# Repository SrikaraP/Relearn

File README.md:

# Relearn

### The AI-Powered Education OS

Relearn is an AI-powered platform that brings students, teachers, and parents into one connected learning ecosystem.

Instead of juggling multiple apps for studying, assignments, communication, and progress tracking, Relearn combines everything into a single intelligent platform.

## Why Relearn?

Education is fragmented.

Students struggle to stay organized, teachers spend hours on repetitive tasks, and parents often lack visibility into academic progress.

Relearn uses AI to simplify learning, automate workflows, and provide personalized insights for everyone involved.

## Key Features

### For Institutions

* Exan Paper Scanning Tool
* Secure File Transfers
* Student File Tracking
* Student Progress Tracking

### For Students

* Personalized learning roadmaps
* AI study assistant
* Smart summaries, flashcards, and quizzes
* Progress tracking and goal setting

### For Teachers

* Question paper and answer sheet analysis
* Performance insights and learning-gap detection
* Automated feedback generation
* Classroom management tools

### For Parents

* Real-time academic visibility
* Progress monitoring
* Personalized learning recommendations

## ReLens

### ReLens Lite

A student-focused scanner that converts notes and worksheets into:

* Summaries
* Flashcards
* Quizzes
* Revision resources

### ReLens Edu

A teacher-focused scanner that analyzes:

* Question papers
* Answer sheets
* Student performance
* Common mistakes and learning gaps

## Tech Stack

* React
* TypeScript
* Vite
* Google Gemini
* OCR & Multimodal AI
* Custom PCB Scanner Hardware

## Vision

To build the operating system for education.

## An insider Look Into the Project

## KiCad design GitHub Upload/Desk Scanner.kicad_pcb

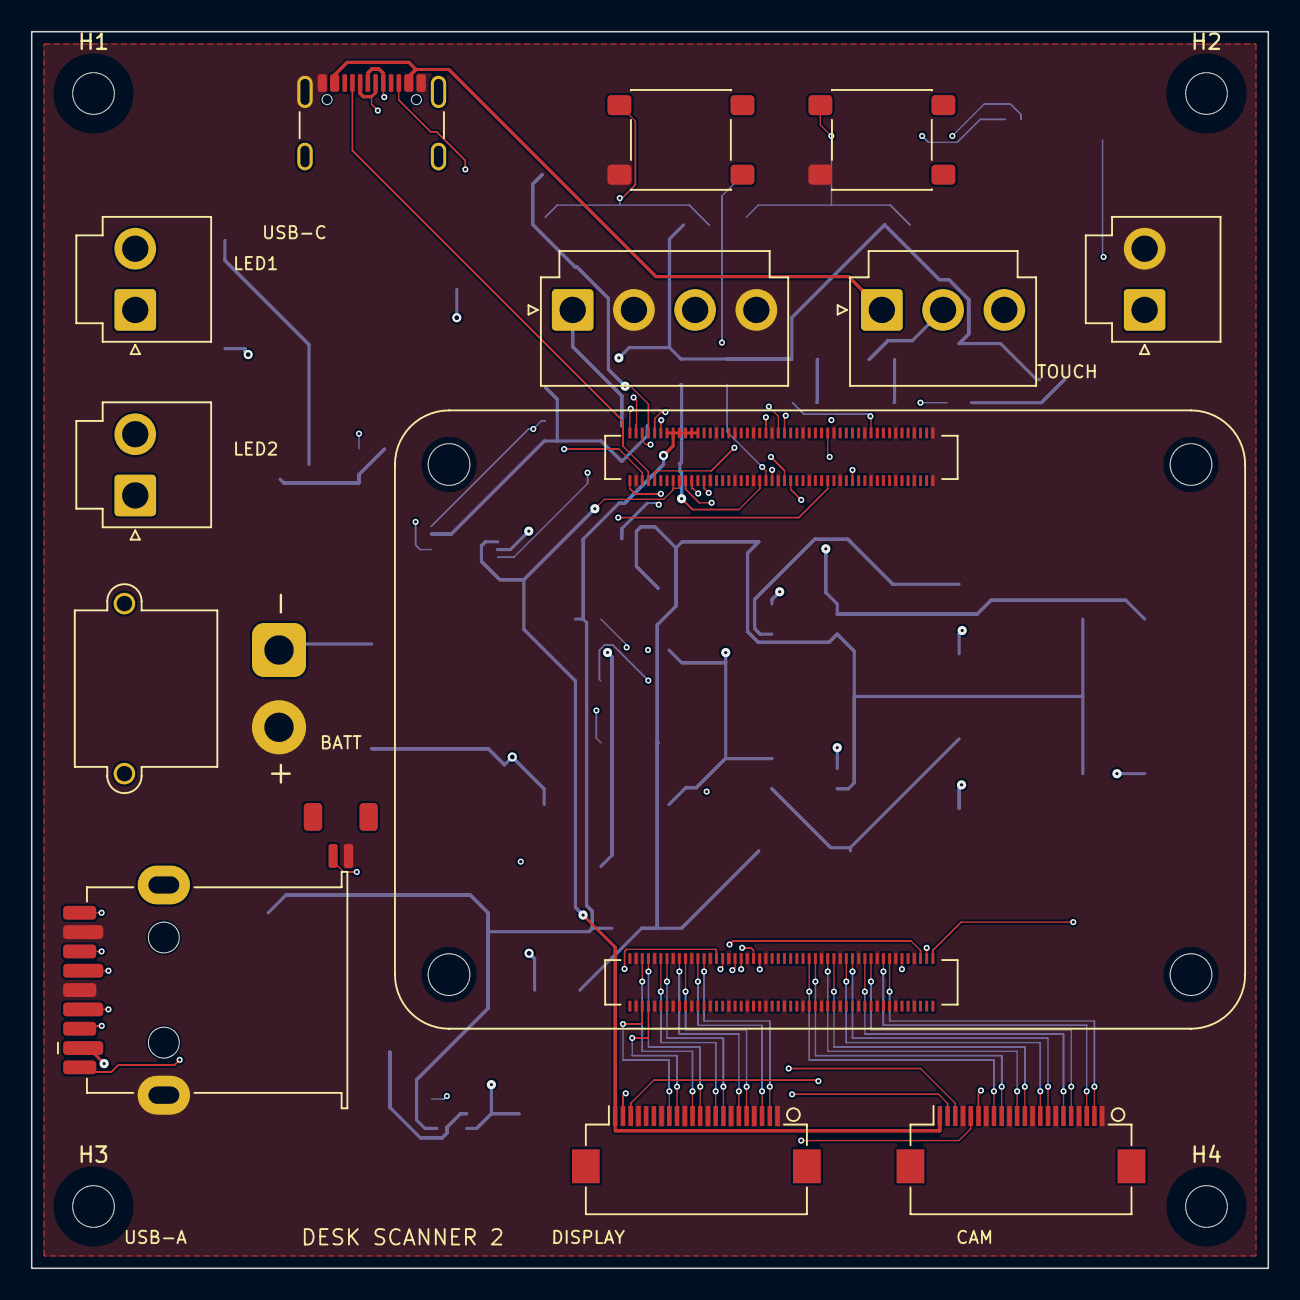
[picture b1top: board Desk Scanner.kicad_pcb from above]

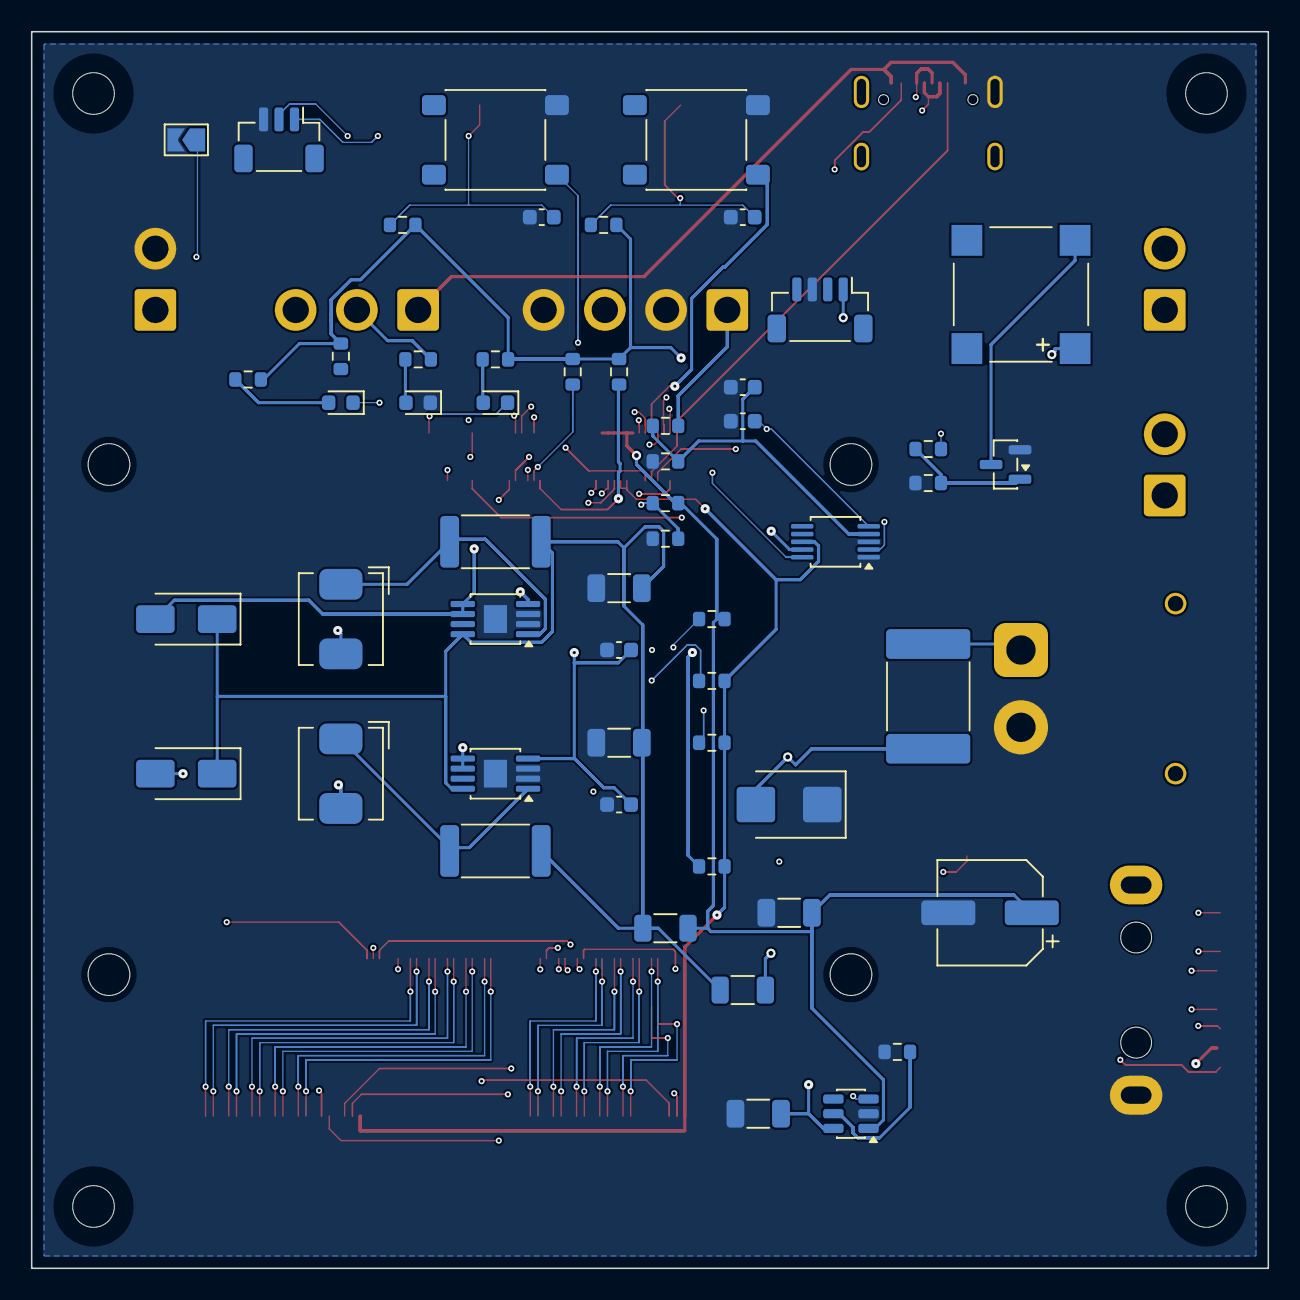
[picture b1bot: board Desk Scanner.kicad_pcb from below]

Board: 4 copper layers, 80.0 x 80.0 mm, 72 parts (54 on the bottom side), 78 nets.

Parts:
BT1: Wired RTC cell input; JST_SH_BM02B-SRSS-TB_1x02-1MP_P1.00mm_Vertical
BZ1: 5V active buzzer; PUIAudio_SMT_0825_S_4_R
C1: 10uF USB VBUS; C_1206_3216Metric
C2: 100uF bulk; CP_Elec_6.3x5.8
C3: 10uF; C_1206_3216Metric
C4, C5: 10uF 50V X7R; C_1206_3216Metric
C6, C7: 1nF soft-start; C_0603_1608Metric
C8, C9: 100nF debounce; C_0603_1608Metric
C10: 100nF BAT filter; C_0603_1608Metric
C11: 100nF 5V filter; C_0603_1608Metric
D2: SMBJ16A TVS; D_SMB
D3, D4: SS34 Schottky; D_SMA
D5: ACT LED green; LED_0603_1608Metric
D6: Power LED; LED_0603_1608Metric
D7: CM5 PWR status LED; LED_0603_1608Metric
F1: 7.5A battery fuse; Fuse_2920_7451Metric
H1, H2, H3, H4: M2.5; MountingHole_2.7mm_M2.5_DIN965
J1: USB-C USB2 Data + 5V Input; USB_C_Receptacle_GCT_USB4105-xx-A_16P_TopMnt_Horizontal
J2: USB-A Host USB3; USB3_A_Receptacle_Wuerth_692122030100
J3: Camera FFC - Raspberry Pi Camera Module 3 AF; Hirose_FH12-22S-0.5SH_1x22-1MP_P0.50mm_Horizontal
J4: Display FFC - Raspberry Pi Touch Display 2; Hirose_FH12-22S-0.5SH_1x22-1MP_P0.50mm_Horizontal
J5: Display 5V Power; JST_VH_B2P-VH_1x02_P3.96mm_Vertical
J6: 3S protected Li-ion pack input XT30; AMASS_XT30PW-M_1x02_P2.50mm_Horizontal
J7: 5V 6A buck regulator module; JST_VH_B4P-VH_1x04_P3.96mm_Vertical
J8: High-current 5V source selector; JST_VH_B3P-VH_1x03_P3.96mm_Vertical
J9: LED bar 1 output; JST_VH_B2P-VH_1x02_P3.96mm_Vertical
J10: LED bar 2 output; JST_VH_B2P-VH_1x02_P3.96mm_Vertical
J11: 5V PWM fan; JST_SH_BM04B-SRSS-TB_1x04-1MP_P1.00mm_Vertical
J12: UART debug 3-pin; JST_SH_BM03B-SRSS-TB_1x03-1MP_P1.00mm_Vertical
JP1: USB OTG ID strap - leave open for device mode; SolderJumper-2_P1.3mm_Open_TrianglePad1.0x1.5mm
L1, L2: 47uH >=2A shielded; L_Bourns_SRP5030CC
Q1: 2N7002 buzzer low-side; SOT-23
R1: 10k USB ILIM set; R_0603_1608Metric
R2: 10k PMIC enable pull-up; R_0603_1608Metric
R3: 10k WLAN enable pull-up; R_0603_1608Metric
R4: 10k Bluetooth enable pull-up; R_0603_1608Metric
R5: 10k boot pull-up; R_0603_1608Metric
R6: 0R LED_SUPPLY from +5V_SYS; R_1206_3216Metric
R7: 0R DNP LED_SUPPLY from BAT_FUSED; R_1206_3216Metric
R8, R9: 0.15R 1% 0.5W LED sense; R_2512_6332Metric
R10, R11: 10k; R_0603_1608Metric
R12: 100R gate; R_0603_1608Metric
R13: 100k gate pulldown; R_0603_1608Metric
R14: 1k ACT; R_0603_1608Metric
R15: 1k PWR; R_0603_1608Metric
R16: 10k tach pull-up; R_0603_1608Metric
R17: 2.2k SDA pull-up; R_0603_1608Metric
R18: 2.2k SCL pull-up; R_0603_1608Metric
R19: 100k BAT top; R_0603_1608Metric
R20: 22k BAT bottom; R_0603_1608Metric
R21: 47k 5V top; R_0603_1608Metric
R22: 47k 5V bottom; R_0603_1608Metric
R23: 1k CM5 PWR; R_0603_1608Metric
SW1: Scan/Capture button; SW_SPST_PTS645Sx43SMTR92
SW2: Lighting level button; SW_SPST_PTS645Sx43SMTR92
SW3: nRPIBOOT recovery; SW_SPST_PTS645Sx43SMTR92
SW4: CM5 power button; SW_SPST_PTS645Sx43SMTR92
U1: Raspberry Pi CM5 Wireless 8GB/64GB eMMC; Raspberry-Pi-5-Compute-Module
U2: AP2553W6 USB Host Power Switch; SOT-23-6
U3: AL8860MP LED driver 1; MSOP-8-1EP_3x3mm_P0.65mm_EP1.5x1.8mm
U4: AL8860MP LED driver 2; MSOP-8-1EP_3x3mm_P0.65mm_EP1.5x1.8mm
U5: ADS1115 battery/system monitor; TSSOP-10_3x3mm_P0.5mm

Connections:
/+3V3_CM5: J3.22, J4.22, R3.1, R4.1, R5.1, R10.1, R11.1, R14.1, R16.1, R17.1, R18.1, R23.1, U1.84, U1.86, U5.8
/+5V_BATREG: J7.3, J8.3
/+5V_SYS: BZ1.1, C2.1, C3.1, J5.1, J8.2, J11.1, R2.1, R6.1, R15.1, R21.1, U1.77, U1.79, U1.81, U1.83, U1.85, U1.87, U2.1
/+5V_USBC: J1.A4, J1.A9, J1.B4, J1.B9, J8.1
/ACT_LED_A: D5.2, R14.2
/ADC_ALERT: U1.54, U5.2
/BAT_FUSED: D2.2, F1.2, J7.1, R7.1, R19.1
/BAT_RAW: F1.1, J6.1
/BAT_SENSE: C10.1, R19.2, R20.1, U5.4
/BTN_LED_MODE: C9.1, R11.2, SW2.1, U1.48
/BTN_SCAN: C8.1, R10.2, SW1.1, U1.50
/BT_nDISABLE: R4.2, U1.91
/BUZZER_GATE: Q1.1, R12.2, R13.1
/BUZZER_GPIO: R12.1, U1.28
/BUZZER_LOW: BZ1.2, Q1.3
/CAM_GPIO0: J3.17, U1.97
/CAM_GPIO1: J3.18, U1.100
/CM5_PWR_LED_A: D7.2, R23.2
/DPHY0_C_N: J3.8, U1.127
/DPHY0_C_P: J3.9, U1.129
/DPHY0_D0_N: J3.2, U1.115
/DPHY0_D0_P: J3.3, U1.117
/DPHY0_D1_N: J3.5, U1.121
/DPHY0_D1_P: J3.6, U1.123
/DPHY0_D2_N: J3.11, U1.133
/DPHY0_D2_P: J3.12, U1.135
/DPHY0_D3_N: J3.14, U1.139
/DPHY0_D3_P: J3.15, U1.141
/DPHY1_C_N: J4.8, U1.187
/DPHY1_C_P: J4.9, U1.189
/DPHY1_D0_N: J4.2, U1.175
/DPHY1_D0_P: J4.3, U1.177
/DPHY1_D1_N: J4.5, U1.181
/DPHY1_D1_P: J4.6, U1.183
/DPHY1_D2_N: J4.11, U1.193
/DPHY1_D2_P: J4.12, U1.195
/DPHY1_D3_N: J4.14, U1.194
/DPHY1_D3_P: J4.15, U1.196
/GND: BT1.2, C1.2, C2.2, C3.2, C4.2, C5.2, C6.2, C7.2, C8.2, C9.2, C10.2, C11.2, D2.1, D6.1, J1.A1, J1.A12, J1.B1, J1.B12, J1.SH, J2.4, J2.7, J2.SH, J3.1, J3.4, J3.7, J3.10, J3.13, J3.16, J3.19, J4.1, J4.4, J4.7, J4.10, J4.13, J4.16, J4.19, J5.2, J6.2, J7.2, J7.4, J11.3, J12.3, JP1.2, Q1.2, R1.2, R13.2, R20.2, R22.2, SW1.2, SW2.2, SW3.2, SW4.2, U1.1, U1.2, U1.7, U1.8, U1.13, U1.14, U1.22, U1.23, U1.32, U1.33, U1.42, U1.43, U1.52, U1.53, U1.59, U1.60, U1.65, U1.66, U1.71, U1.74, U1.98, U1.107, U1.108, U1.113, U1.114, U1.119, U1.120, U1.125, U1.126, U1.131, U1.132, U1.137, U1.138, U1.144, U1.150, U1.155, U1.156, U1.161, U1.162, U1.167, U1.168, U1.173, U1.174, U1.179, U1.180, U1.185, U1.186, U1.191, U1.192, U1.197, U1.198, U2.2, U3.2, U3.3, U3.9, U4.2, U4.3, U4.9, U5.1, U5.3
/I2C1_SCL: R18.2, U1.56, U5.10
/I2C1_SDA: R17.2, U1.58, U5.9
/LED1_A: J9.1, L1.2
/LED1_K: D3.2, J9.2, U3.5, U3.6
/LED1_SET: L1.1, R8.2, U3.1
/LED2_A: J10.1, L2.2
/LED2_K: D4.2, J10.2, U4.5, U4.6
/LED2_SET: L2.1, R9.2, U4.1
/LED_PWM: C6.1, C7.1, U1.49, U3.4, U4.4
/LED_SUPPLY: C4.1, C5.1, D3.1, D4.1, R6.2, R7.2, R8.1, R9.1, U3.8, U4.8
/LED_nACT: D5.1, U1.21
/LED_nPWR: D7.1, U1.95
/PMIC_ENABLE: R2.2, U1.99
/PWR_BUT: SW4.1, U1.92
/PWR_LED_A: D6.2, R15.2
/SCL0_CAM: J3.20, U1.80
/SCL1_DSI: J4.20, U1.35
/SDA0_CAM: J3.21, U1.82
/SDA1_DSI: J4.21, U1.36
/SYS5_SENSE: C11.1, R21.2, R22.1, U5.5
/UART_RXD: J12.2, U1.51
/UART_TXD: J12.1, U1.55
/USB2_N: J1.A7, J1.B7, U1.103
/USB2_P: J1.A6, J1.B6, U1.105
/USB3_1_D_N: J2.2, U1.165
/USB3_1_D_P: J2.3, U1.163
/USB3_1_RX_N: J2.6, U1.157
/USB3_1_RX_P: J2.5, U1.159
/USB3_1_TX_N: J2.9, U1.169
/USB3_1_TX_P: J2.8, U1.171
/USB_A_VBUS: C1.1, J2.1, U2.6
/USB_C_CC1: J1.A5, U1.94
/USB_C_CC2: J1.B5, U1.96
/USB_ILIM: R1.1, U2.5
/USB_OTG_ID: JP1.1, U1.101
/VBAT: BT1.1, U1.76
/VBUS_EN: U1.111, U2.3
/WL_nDISABLE: R3.2, U1.89
/nRPIBOOT: R5.2, SW3.1, U1.93

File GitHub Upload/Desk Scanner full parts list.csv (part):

Qty,References,Common name,PCB value,KiCad footprint,Install / buy status,Separate item to plug in
"1","BT1","Wired RTC coin-cell connector","Wired RTC cell input",":JST_SH_BM02B-SRSS-TB_1x02-1MP_P1.00mm_Vertical","PCB connector; wired RTC cell is separate","Wired RTC/coin-cell battery"
"1","BZ1","Active magnetic buzzer","5V active buzzer","Buzzer_Beeper:PUIAudio_SMT_0825_S_4_R","Buy and solder/assemble onto PCB",""
"1","C1","SMD capacitor","10uF USB VBUS","Capacitor_SMD:C_1206_3216Metric","Buy and solder/assemble onto PCB",""
"1","C10","SMD capacitor","100nF BAT filter","Capacitor_SMD:C_0603_1608Metric","Buy and solder/assemble onto PCB",""
"1","C11","SMD capacitor","100nF 5V filter","Capacitor_SMD:C_0603_1608Metric","Buy and solder/assemble onto PCB",""
"1","C2","SMD capacitor","100uF bulk","Capacitor_SMD:CP_Elec_6.3x5.8","Buy and solder/assemble onto PCB",""
"1","C3","SMD capacitor","10uF","Capacitor_SMD:C_1206_3216Metric","Buy and solder/assemble onto PCB",""
"2","C4, C5","SMD capacitor","10uF 50V X7R","Capacitor_SMD:C_1206_3216Metric","Buy and solder/assemble onto PCB",""
"2","C6, C7","SMD capacitor","1nF soft-start","Capacitor_SMD:C_0603_1608Metric","Buy and solder/assemble onto PCB",""
"2","C8, C9","SMD capacitor","100nF debounce","Capacitor_SMD:C_0603_1608Metric","Buy and solder/assemble onto PCB",""
"1","D2","TVS protection diode","SMBJ16A TVS","Diode_SMD:D_SMB","Buy and solder/assemble onto PCB",""
"2","D3, D4","Schottky diode","SS34 Schottky","Diode_SMD:D_SMA","Buy and solder/assemble onto PCB",""
"1","D5","Indicator LED","ACT LED green","LED_SMD:LED_0603_1608Metric","Buy and solder/assemble onto PCB",""
"1","D6","Indicator LED","Power LED","LED_SMD:LED_0603_1608Metric","Buy and solder/assemble onto PCB",""
"1","D7","Indicator LED","CM5 PWR status LED","LED_SMD:LED_0603_1608Metric","Buy and solder/assemble onto PCB",""
"1","F1","Blade/holder fuse footprint","7.5A battery fuse","Fuse:Fuse_2920_7451Metric","Buy and solder/assemble onto PCB",""
"4","H1, H2, H3, H4","M2.5 mounting hole","M2.5",":MountingHole_2.7mm_M2.5_DIN965","Fabricated in PCB; buy M2.5 screws/standoffs separately if needed","M2.5 screw/standoff"
"1","J1","USB-C receptacle","USB-C USB2 Data + 5V Input","Connector_USB:USB_C_Receptacle_GCT_USB4105-xx-A_16P_TopMnt_Horizontal","Soldered to PCB; USB-C cable/host computer is separate","USB-C cable to computer/power"
"1","J10","LED bar output connector","LED bar 2 output","Connector_JST:JST_VH_B2P-VH_1x02_P3.96mm_Vertical","PCB connector; LED bar/light assembly is separate","External LED bar 2"
"1","J11","Optional fan connector","5V PWM fan","Connector_JST:JST_SH_BM04B-SRSS-TB_1x04-1MP_P1.00mm_Vertical","Optional/DNP unless using a power-only 5V fan","Optional 5V fan"
"1","J12","UART debug header","UART debug 3-pin","Connector_JST:JST_SH_BM03B-SRSS-TB_1x03-1MP_P1.00mm_Vertical","Optional debug header; plug USB-UART adapter separately","Optional USB-UART adapter/cable"
"1","J2","USB-A receptacle","USB-A Host USB3","Connector_USB:USB3_A_Receptacle_Wuerth_692122030100","Soldered to PCB; USB device/cable is separate","USB-A plug/cable/device"
"1","J3","22-pin camera FFC connector","Camera FFC - Raspberry Pi Camera Module 3 AF","CM5IO:Hirose_FH12-22S-0.5SH_1x22-1MP_P0.50mm_Horizontal","PCB connector; buy camera module separately and plug in by FFC","Raspberry Pi Camera Module 3 Autofocus and 22-pin FFC"
"1","J4","22-pin display DSI FFC connector","Display FFC - Raspberry Pi Touch Display 2","CM5IO:Hirose_FH12-22S-0.5SH_1x22-1MP_P0.50mm_Horizontal","PCB connector; buy Raspberry Pi Touch Display 2 separately and plug in by FFC","Raspberry Pi Touch Display 2, 5-inch, and correct DSI FFC"
"1","J5","Display power connector/header","Display 5V Power","Connector_JST:JST_VH_B2P-VH_1x02_P3.96mm_Vertical","PCB connector/header; display power cable/display are separate","Display 5V power lead"
"1","J6","XT30 battery connector","3S protected Li-ion pack input XT30","Connector_AMASS:AMASS_XT30PW-M_1x02_P2.50mm_Horizontal","PCB connector; 3S protected Li-ion pack is separate","3S protected Li-ion battery pack with XT30 mating connector"
"1","J7","Buck-regulator module header","5V 6A buck regulator module","Connector_JST:JST_VH_B4P-VH_1x04_P3.96mm_Vertical","PCB header; 5V 6A buck regulator module is separate","5V 6A buck regulator module"
"1","J8","5V source-selector/header","High-current 5V source selector","Connector_JST:JST_VH_B3P-VH_1x03_P3.96mm_Vertical","Buy and solder/assemble onto PCB","Jumper/shunt or wired source-select link as implemented"
"1","J9","LED bar output connector","LED bar 1 output","Connector_JST:JST_VH_B2P-VH_1x02_P3.96mm_Vertical","PCB connector; LED bar/light assembly is separate","External LED bar 1"
"1","JP1","Solder jumper","USB OTG ID strap - leave open for device mode","Jumper:SolderJumper-2_P1.3mm_Open_TrianglePad1.0x1.5mm","PCB solder jumper; no separate part unless fitting a 0R link",""
"2","L1, L2","Shielded power inductor","47uH >=2A shielded","CM5IO:L_Bourns_SRP5030CC","Buy and solder/assemble onto PCB",""
"1","Q1","Small-signal N-MOSFET","2N7002 buzzer low-side","Package_TO_SOT_SMD:SOT-23","Buy and solder/assemble onto PCB",""
"1","R1","SMD resistor","10k USB ILIM set","Resistor_SMD:R_0603_1608Metric","Buy and solder/assemble onto PCB",""
"2","R10, R11","SMD resistor","10k","Resistor_SMD:R_0603_1608Metric","Buy and solder/assemble onto PCB",""
"1","R12","SMD resistor","100R gate","Resistor_SMD:R_0603_1608Metric","Buy and solder/assemble onto PCB",""
"1","R13","SMD resistor","100k gate pulldown","Resistor_SMD:R_0603_1608Metric","Buy and solder/assemble onto PCB",""
"1","R14","SMD resistor","1k ACT","Resistor_SMD:R_0603_1608Metric","Buy and solder/assemble onto PCB",""
"1","R15","SMD resistor","1k PWR","Resistor_SMD:R_0603_1608Metric","Buy and solder/assemble onto PCB",""
"1","R16","SMD resistor","10k tach pull-up","Resistor_SMD:R_0603_1608Metric","DNP option; fan tach was left unused",""
"1","R17","SMD resistor","2.2k SDA pull-up","Resistor_SMD:R_0603_1608Metric","Buy and solder/assemble onto PCB",""
"1","R18","SMD resistor","2.2k SCL pull-up","Resistor_SMD:R_0603_1608Metric","Buy and solder/assemble onto PCB",""
"1","R19","SMD resistor","100k BAT top","Resistor_SMD:R_0603_1608Metric","Buy and solder/assemble onto PCB",""
"1","R2","SMD resistor","10k PMIC enable pull-up","Resistor_SMD:R_0603_1608Metric","Buy and solder/assemble onto PCB",""
"1","R20","SMD resistor","22k BAT bottom","Resistor_SMD:R_0603_1608Metric","Buy and solder/assemble onto PCB",""
"1","R21","SMD resistor","47k 5V top","Resistor_SMD:R_0603_1608Metric","Buy and solder/assemble onto PCB",""
"1","R22","SMD resistor","47k 5V bottom","Resistor_SMD:R_0603_1608Metric","Buy and solder/assemble onto PCB",""
"1","R23","SMD resistor","1k CM5 PWR","Resistor_SMD:R_0603_1608Metric","Buy and solder/assemble onto PCB",""
"1","R3","SMD resistor","10k WLAN enable pull-up","Resistor_SMD:R_0603_1608Metric","Buy and solder/assemble onto PCB",""
"1","R4","SMD resistor","10k Bluetooth enable pull-up","Resistor_SMD:R_0603_1608Metric","Buy and solder/assemble onto PCB",""
"1","R5","SMD resistor","10k boot pull-up","Resistor_SMD:R_0603_1608Metric","Buy and solder/assemble onto PCB",""
"1","R6","SMD resistor","0R LED_SUPPLY from +5V_SYS","Resistor_SMD:R_1206_3216Metric","Buy and solder/assemble onto PCB",""
"1","R7","SMD resistor","0R DNP LED_SUPPLY from BAT_FUSED","Resistor_SMD:R_1206_3216Metric","DNP option; do not fit for normal +5V_SYS LED supply",""
"2","R8, R9","SMD resistor","0.15R 1% 0.5W LED sense","Resistor_SMD:R_2512_6332Metric","Buy and solder/assemble onto PCB",""
"1","SW1","Tactile pushbutton switch","Scan/Capture button","Button_Switch_SMD:SW_SPST_PTS645Sx43SMTR92","Buy and solder/assemble onto PCB",""
"1","SW2","Tactile pushbutton switch","Lighting level button","Button_Switch_SMD:SW_SPST_PTS645Sx43SMTR92","Buy and solder/assemble onto PCB",""
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
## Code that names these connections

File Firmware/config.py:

"""
Desk Scanner Firmware — Configuration
All settings derived from schematic analysis of Desk_Scanner.kicad_sch.

GPIO pin numbers are BCM (Broadcom) numbers for the CM5.
Confirmed from schematic net-label to CM5 pin-position mapping.
"""

# ─── GPIO PINS (BCM numbering) ──────────────────────────────────────────────
# Confirmed from schematic net labels at their exact y-positions on CM5 symbol
# (origin at x=69.85, y=105.41; abs_y = origin_y - sym_y)

GPIO_I2C_SDA      = 2   # I2C1_SDA → ADS1115 (pin #58 on CM5 connector)
GPIO_I2C_SCL      = 3   # I2C1_SCL → ADS1115 (pin #56)
GPIO_ADC_ALERT    = 4   # ADC_ALERT from ADS1115 ALERT/RDY (pin #54)
GPIO_BUZZER       = 13  # BUZZER_GPIO → Q1 MOSFET gate (pin #28)
GPIO_UART_TXD     = 14  # UART debug TX (pin #55) — handled by OS
GPIO_UART_RXD     = 15  # UART debug RX (pin #51) — handled by OS
GPIO_BTN_SCAN     = 17  # BTN_SCAN → SW1 Scan/Capture button (pin #50), active LOW
GPIO_LED_PWM      = 18  # LED_PWM → AL8860MP DIM pins on U3 & U4 (pin #49), HW-PWM
GPIO_BTN_LIGHTING = 27  # BTN_LED_MODE → SW2 Lighting level button (pin #48), active LOW
# SW3 → nRPIBOOT (CM5 pin #93, dedicated recovery pin, not a BCM GPIO)
# SW4 → PWR_BUT  (CM5 pin #92, dedicated power button, not a BCM GPIO)

# ─── I2C / ADS1115 ──────────────────────────────────────────────────────────
I2C_BUS           = 1      # /dev/i2c-1 (GPIO2/GPIO3 = I2C1)
ADS1115_ADDR      = 0x48   # ADDR pin → GND (default address)
ADS1115_PGA       = 4.096  # Volts full-scale (PGA = ±4.096 V)

# Voltage divider ratios (from schematic)
# BAT_SENSE: R19 (100k top) / R20 (22k bottom)  →  22k / 122k = 0.18033
# SYS5_SENSE: R21 (47k top) / R22 (47k bottom)  →  47k / 94k  = 0.50000
BAT_DIVIDER_RATIO   = 22.0 / (100.0 + 22.0)  # = 0.18033
SYS5_DIVIDER_RATIO  = 47.0 / (47.0 + 47.0)   # = 0.50000

# 3S Li-ion thresholds (volts on battery pack)
BAT_FULL_V   = 12.6  # 4.20 V × 3 cells
BAT_NOM_V    = 11.1  # 3.70 V × 3 cells
BAT_LOW_V    = 9.9   # 3.30 V × 3 cells (warn)
BAT_CUTOFF_V = 9.0   # 3.00 V × 3 cells (critical)

# ─── LED LIGHTING ───────────────────────────────────────────────────────────
# AL8860MP DIM pin: 100 Hz – 50 kHz PWM, 0 % duty = off, 100 % = full brightness
LED_PWM_FREQUENCY = 1000   # 1 kHz — well within AL8860MP DIM range
LED_BRIGHTNESS_LEVELS = [25, 50, 75, 100]   # % — cycled by SW2
LED_DEFAULT_LEVEL  = 75    # percent on startup

# ─── CAMERA ─────────────────────────────────────────────────────────────────
# Raspberry Pi Camera Module 3 (IMX708, 12MP) on MIPI0 (J3 connector)
CAMERA_MAX_RES     = (4608, 2592)   # Full 12 MP
CAMERA_PREVIEW_RES = (1280, 720)    # Preview stream to web UI
CAMERA_JPEG_QUALITY = 95            # 0-100 for captured stills
SCAN_DPI           = 300            # DPI stored in JPEG EXIF + PDF metadata
AF_SETTLE_TIME     = 0.8            # seconds to allow autofocus to settle

# ─── PDF ────────────────────────────────────────────────────────────────────
PDF_OUTPUT_DIR     = "/var/scanner/pdfs"   # also served via Samba
PDF_TEMP_DIR       = "/var/scanner/tmp"
PDF_AUTHOR         = "Desk Scanner"
PDF_PRODUCER       = "Desk Scanner Firmware"

# ─── NETWORK ────────────────────────────────────────────────────────────────
AP_SSID            = "DeskScanner"
AP_PASSWORD        = "scanner123"    # WPA2 password; set "" for open network
AP_IP              = "10.42.0.1"
AP_DHCP_RANGE      = ("10.42.0.10", "10.42.0.100")
AP_CHANNEL         = 6
MDNS_HOSTNAME      = "scanner"      # reachable as scanner.local
WEB_PORT           = 80

SAMBA_SHARE_NAME   = "Scans"        # \\scanner.local\Scans
SAMBA_COMMENT      = "Desk Scanner PDFs"

# ─── BUZZER PATTERNS ─────────────────────────────────────────────────────────
# Each tuple: (on_ms, off_ms)  — sequence of beep/pause pairs
BEEP_SCAN_START    = [(80, 40), (80, 0)]     # double-blip when scan begins
BEEP_SCAN_DONE     = [(120, 0)]              # single tone when image captured
BEEP_PDF_READY     = [(100, 80), (100, 80), (200, 0)]  # triple rising tone
BEEP_ERROR         = [(500, 0)]              # long error buzz

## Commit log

2026-06-13 Update README with additional tex
2026-06-14 Software Upload
2026-06-14 Create sjf
2026-06-14 Rename Scanning Tool to Exan Paper Scanning Tool
